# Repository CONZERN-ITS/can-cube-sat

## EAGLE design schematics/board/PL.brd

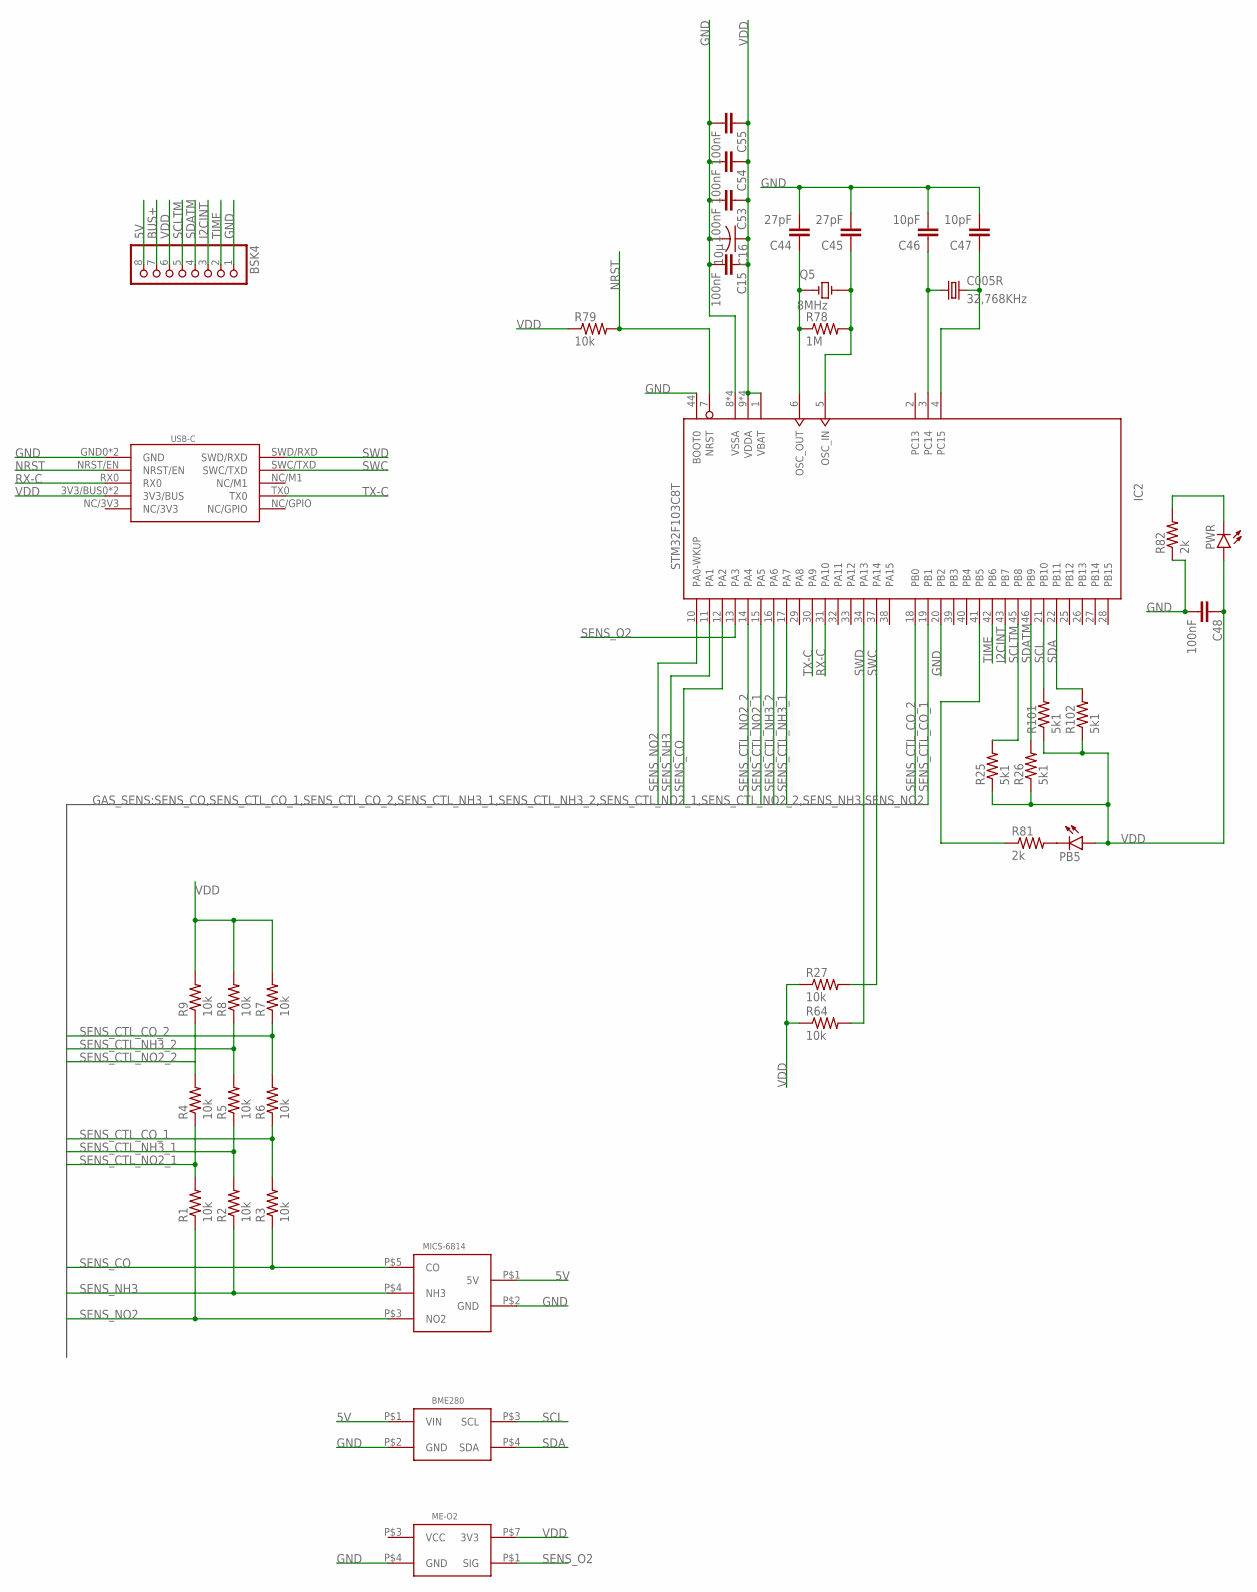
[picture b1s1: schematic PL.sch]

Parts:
BME280: BME280
BSK4: PINHD-1X8; 1X08
C005R: 32,768KHz; C005R
C15, C48, C53, C54, C55: 100nF; C0603
C16: 10µ; C1206
C44, C45: 27pF; C0603
C46, C47: 10pF; C0603
IC2: STM32F103C8T; LQFP48
ME-O2: ME-O2
MICS-6814: MICS-6814
PB5: LEDCHIPLED_0603; CHIPLED_0603
PWR: LEDCHIPLED_0603; CHIPLED_0603
Q5: 8MHz; XTAL_9C-8.000MEEJ-T
R1, R2, R3, R4, R5, R6, R7, R8, R9, R27, R64, R79: 10k; R0603
R25, R26, R101, R102: 5k1; R0603
R78: 1M; R0603
R81, R82: 2k; R0603
USB-C: USB-C

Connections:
5V: BME280.P$1 (VIN), BSK4.8, MICS-6814.P$1 (5V)
BUS+: BSK4.7
GND: BME280.P$2 (GND), BSK4.1, C15.2, C16.2, C44.2, C45.2, C46.2, C47.2, C48.2, C53.2, C54.2, C55.2, IC2.8 (VSSA), IC2.20 (PB2), IC2.23 (VSSA), IC2.35 (VSSA), IC2.44 (BOOT0), IC2.47 (VSSA), ME-O2.P$4 (GND), MICS-6814.P$2 (GND), R82.1, USB-C.GND0 (GND), USB-C.GND1 (GND)
I2CINT: BSK4.3, IC2.43 (PB7)
unnamed: PB5.C, R81.2
unnamed: C44.1, IC2.6 (OSC_OUT), Q5.1, R78.1
unnamed: C45.1, IC2.5 (OSC_IN), Q5.2, R78.2
unnamed: C005R.P$2 (2), C47.1, IC2.4 (PC15)
unnamed: C005R.P$1 (1), C46.1, IC2.3 (PC14)
unnamed: PWR.C, R82.2
unnamed: IC2.41 (PB5), R81.1
NRST: IC2.7 (NRST), R79.2, USB-C.NRST/EN
RX-C: IC2.31 (PA10), USB-C.RX0
SCL: BME280.P$3 (SCL), IC2.21 (PB10), R101.2
SCLTM: BSK4.5, IC2.45 (PB8), R25.2
SDA: BME280.P$4 (SDA), IC2.22 (PB11), R102.2
SDATM: BSK4.4, IC2.46 (PB9), R26.2
SENS_CO: IC2.12 (PA2), MICS-6814.P$5 (CO), R3.1
SENS_CTL_CO_1: IC2.19 (PB1), R3.2, R6.1
SENS_CTL_CO_2: IC2.18 (PB0), R6.2, R7.1
SENS_CTL_NH3_1: IC2.17 (PA7), R2.2, R5.1
SENS_CTL_NH3_2: IC2.16 (PA6), R5.2, R8.1
SENS_CTL_NO2_1: IC2.15 (PA5), R1.2, R4.1
SENS_CTL_NO2_2: IC2.14 (PA4), R4.2, R9.1
SENS_NH3: IC2.11 (PA1), MICS-6814.P$4 (NH3), R2.1
SENS_NO2: IC2.10 (PA0-WKUP), MICS-6814.P$3 (NO2), R1.1
SENS_O2: IC2.13 (PA3), ME-O2.P$1 (SIG)
SWC: IC2.37 (PA14), R27.2, USB-C.SWC/TXD
SWD: IC2.34 (PA13), R64.2, USB-C.SWD/RXD
TIME: BSK4.2, IC2.42 (PB6)
TX-C: IC2.30 (PA9), USB-C.TX0
VDD: BSK4.6, C15.1, C16.1, C48.1, C53.1, C54.1, C55.1, IC2.1 (VBAT), IC2.9 (VDDA), IC2.24 (VDDA), IC2.36 (VDDA), IC2.48 (VDDA), ME-O2.P$7 (3V3), PB5.A, PWR.A, R7.2, R8.2, R9.2, R25.1, R26.1, R27.1, R64.1, R79.1, R101.1, R102.1, USB-C.3V3/BUS0 (3V3/BUS), USB-C.3V3/BUS1 (3V3/BUS)

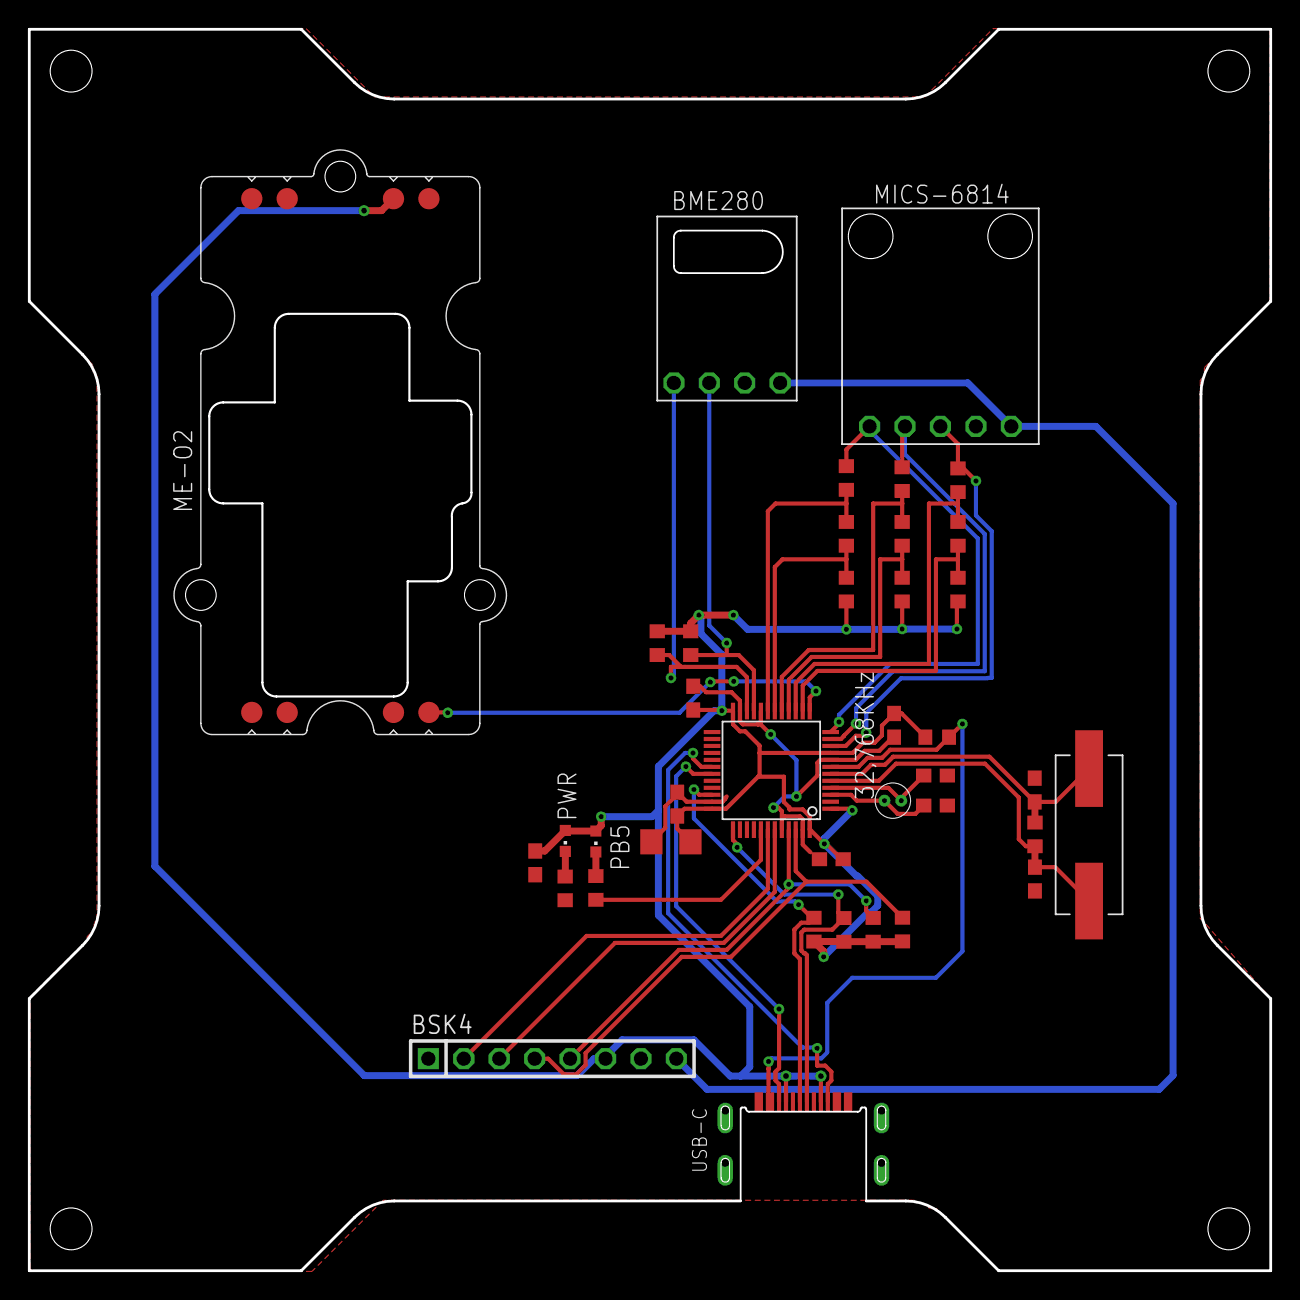
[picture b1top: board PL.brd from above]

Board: 2 copper layers, 89.0 x 89.0 mm, 39 parts (0 on the bottom side), 31 nets.

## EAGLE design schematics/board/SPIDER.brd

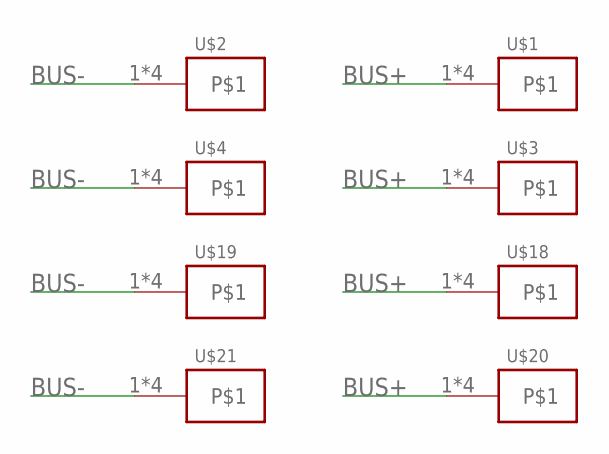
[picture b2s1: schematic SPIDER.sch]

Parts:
U$1, U$2, U$3, U$4, U$18, U$19, U$20, U$21: KCONNECT-

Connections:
BUS+: U$1.1, U$1.2, U$1.3, U$1.4, U$3.1, U$3.2, U$3.3, U$3.4, U$18.1, U$18.2, U$18.3, U$18.4, U$20.1, U$20.2, U$20.3, U$20.4
BUS-: U$2.1, U$2.2, U$2.3, U$2.4, U$4.1, U$4.2, U$4.3, U$4.4, U$19.1, U$19.2, U$19.3, U$19.4, U$21.1, U$21.2, U$21.3, U$21.4

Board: 2 copper layers, 8 parts (0 on the bottom side), 2 nets, no tracks yet.

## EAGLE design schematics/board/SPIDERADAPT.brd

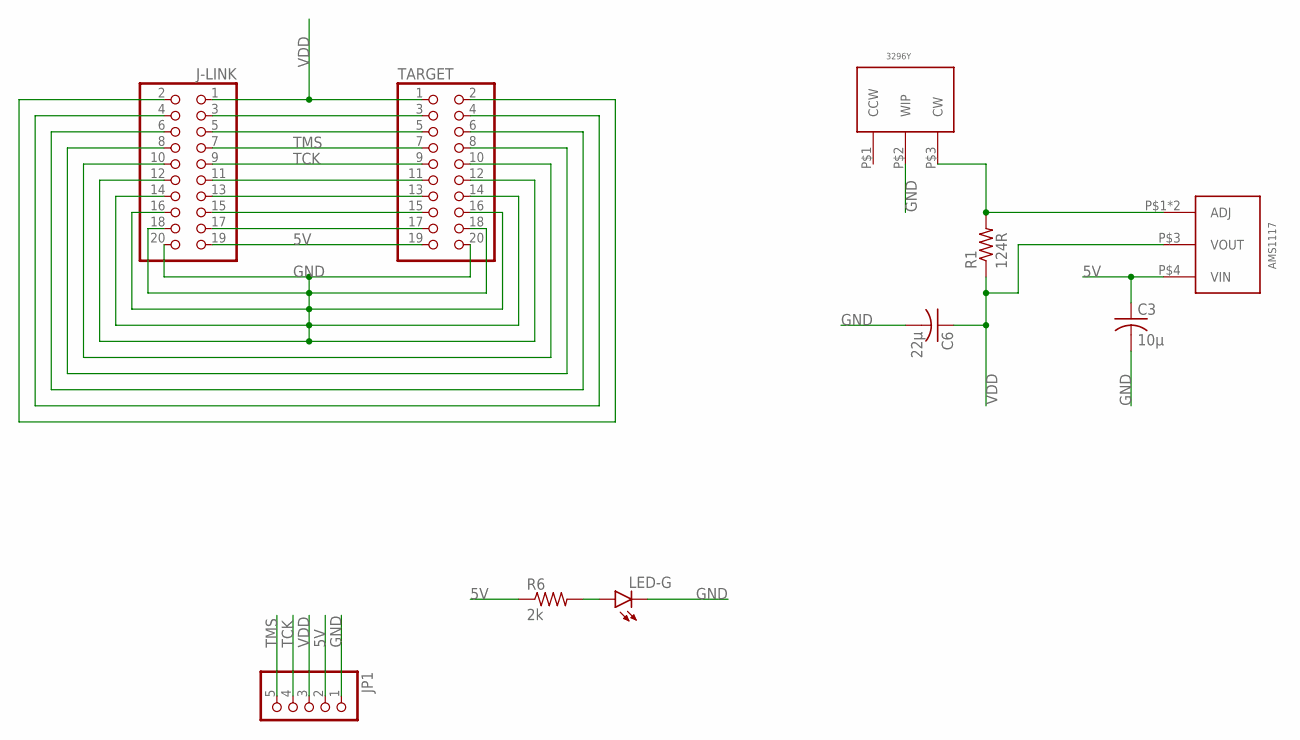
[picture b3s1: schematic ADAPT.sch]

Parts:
3296Y: 3296Y
AMS1117: AMS1117
C3: 10µ; C1206
C6: 22µ; C1206
J-LINK: PINHD-2X10; 2X10
JP1: PINHD-1X5; 1X05
LED-G: LEDCHIPLED_0603; CHIPLED_0603
R1: 124R; R0805
R6: 2k; R0603
TARGET: PINHD-2X10; 2X10

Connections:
5V: AMS1117.P$4 (VIN), C3.1, J-LINK.19, JP1.2, R6.1, TARGET.19
GND1: 3296Y.P$2 (WIP), C3.2, C6.2, J-LINK.12, J-LINK.14, J-LINK.16, J-LINK.18, J-LINK.20, JP1.1, LED-G.C, TARGET.12, TARGET.14, TARGET.16, TARGET.18, TARGET.20
unnamed: J-LINK.3, TARGET.3
unnamed: J-LINK.5, TARGET.5
unnamed: J-LINK.11, TARGET.11
unnamed: J-LINK.13, TARGET.13
unnamed: J-LINK.15, TARGET.15
unnamed: J-LINK.17, TARGET.17
unnamed: J-LINK.10, TARGET.10
unnamed: J-LINK.8, TARGET.8
unnamed: J-LINK.6, TARGET.6
unnamed: J-LINK.4, TARGET.4
unnamed: J-LINK.2, TARGET.2
unnamed 31: 3296Y.P$3 (CW), AMS1117.P$1 (ADJ), AMS1117.P$2 (ADJ), R1.2; also elsewhere on the board
unnamed: LED-G.A, R6.2
TCK: J-LINK.9, JP1.4, TARGET.9
TMS: J-LINK.7, JP1.5, TARGET.7
VDD: AMS1117.P$3 (VOUT), C6.1, J-LINK.1, JP1.3, R1.1, TARGET.1; also elsewhere on the board

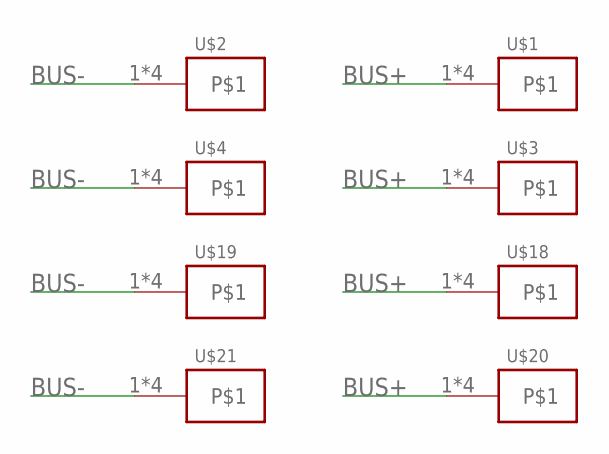
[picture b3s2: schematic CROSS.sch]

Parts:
U$1, U$2, U$3, U$4, U$18, U$19, U$20, U$21: KCONNECT-

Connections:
BUS+: U$1.1, U$1.2, U$1.3, U$1.4, U$3.1, U$3.2, U$3.3, U$3.4, U$18.1, U$18.2, U$18.3, U$18.4, U$20.1, U$20.2, U$20.3, U$20.4
BUS-: U$2.1, U$2.2, U$2.3, U$2.4, U$4.1, U$4.2, U$4.3, U$4.4, U$19.1, U$19.2, U$19.3, U$19.4, U$21.1, U$21.2, U$21.3, U$21.4

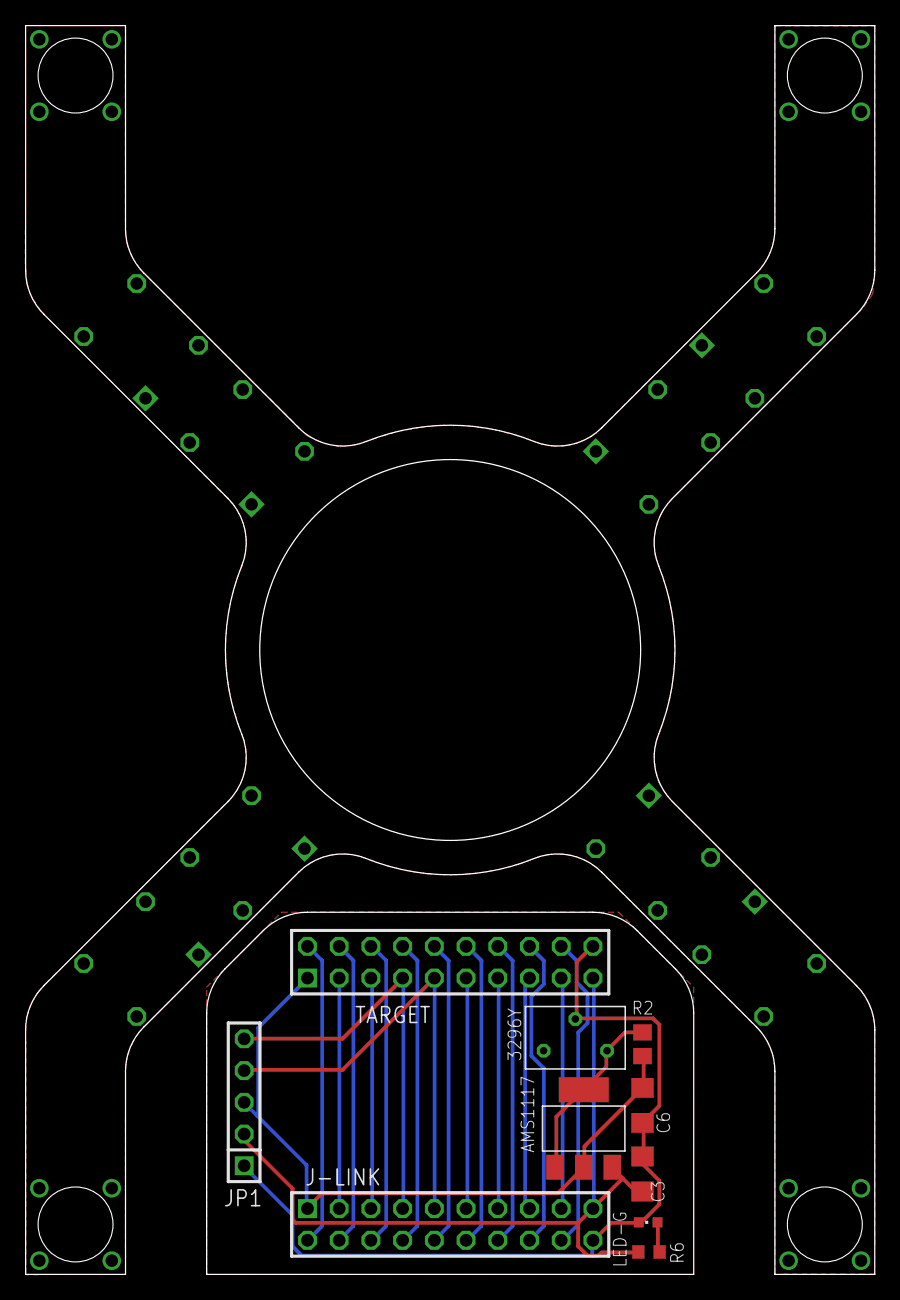
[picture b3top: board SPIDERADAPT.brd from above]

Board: 2 copper layers, 68.0 x 100.0 mm, 18 parts (0 on the bottom side), 20 nets.

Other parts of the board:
R2: 124R; R0805

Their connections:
unnamed 31: R2.2; also elsewhere on the board
VDD: R2.1; also elsewhere on the board

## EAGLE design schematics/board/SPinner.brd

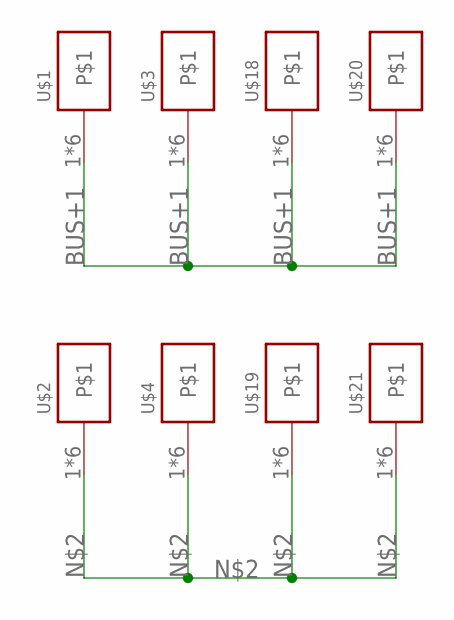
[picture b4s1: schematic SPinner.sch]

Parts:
U$1, U$2, U$3, U$4, U$18, U$19, U$20, U$21: KCONNECT

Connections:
BUS+1: U$1.1, U$1.2, U$1.3, U$1.4, U$1.P$1, U$1.P$2, U$3.1, U$3.2, U$3.3, U$3.4, U$3.P$1, U$3.P$2, U$18.1, U$18.2, U$18.3, U$18.4, U$18.P$1, U$18.P$2, U$20.1, U$20.2, U$20.3, U$20.4, U$20.P$1, U$20.P$2
unnamed: U$2.1, U$2.2, U$2.3, U$2.4, U$2.P$1, U$2.P$2, U$4.1, U$4.2, U$4.3, U$4.4, U$4.P$1, U$4.P$2, U$19.1, U$19.2, U$19.3, U$19.4, U$19.P$1, U$19.P$2, U$21.1, U$21.2, U$21.3, U$21.4, U$21.P$1, U$21.P$2

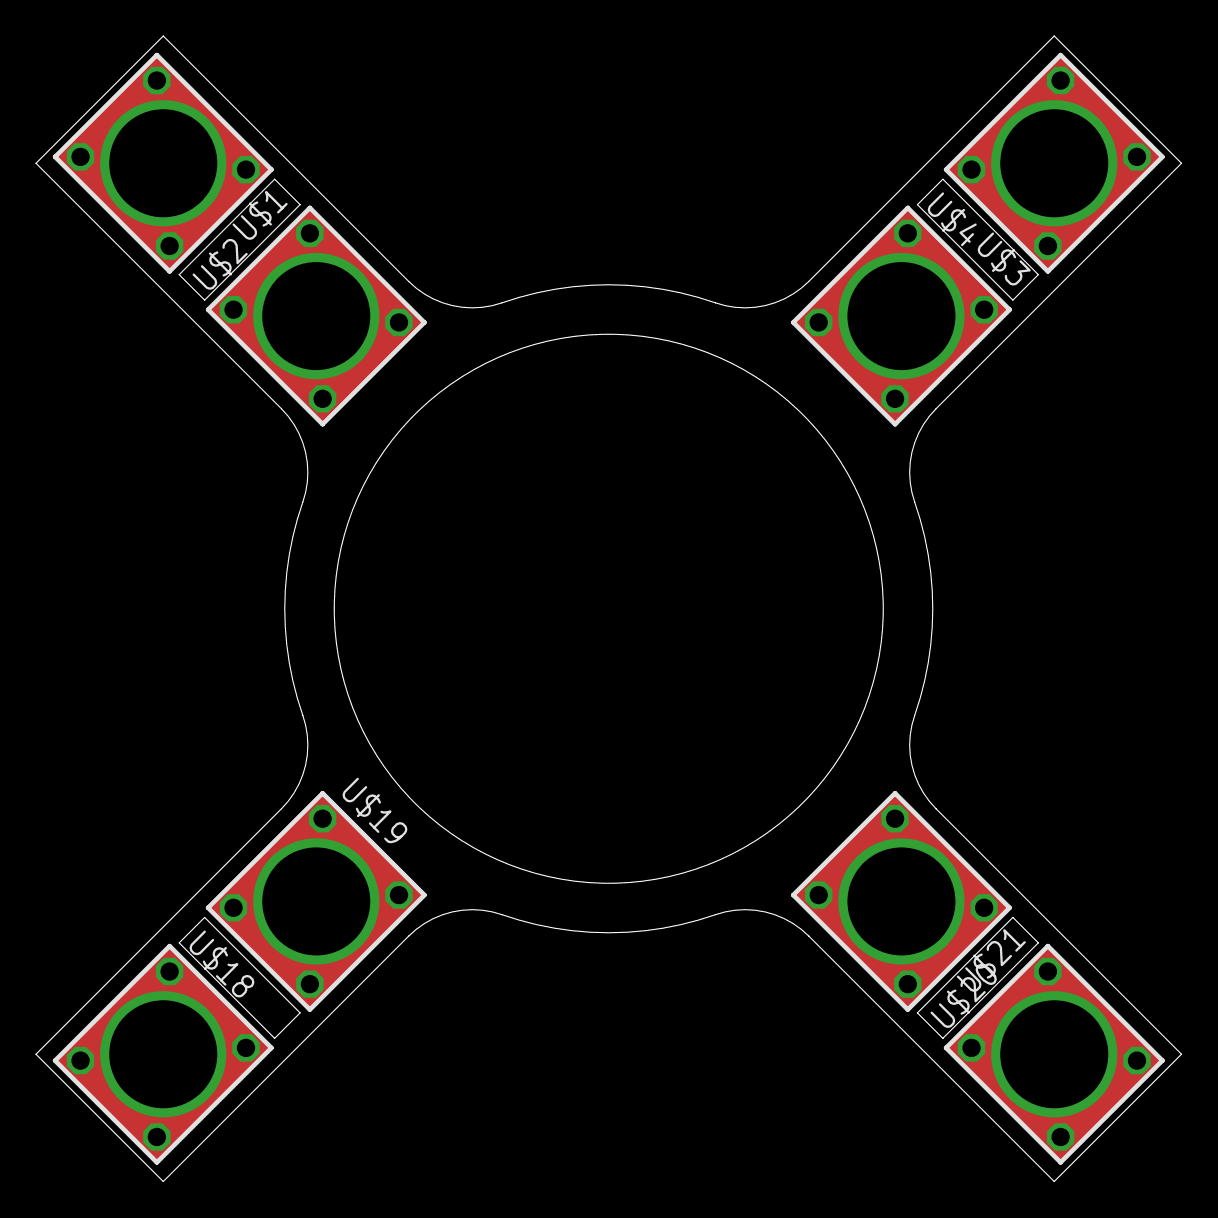
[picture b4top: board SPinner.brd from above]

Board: 2 copper layers, 63.6 x 63.6 mm, 8 parts (0 on the bottom side), 2 nets.

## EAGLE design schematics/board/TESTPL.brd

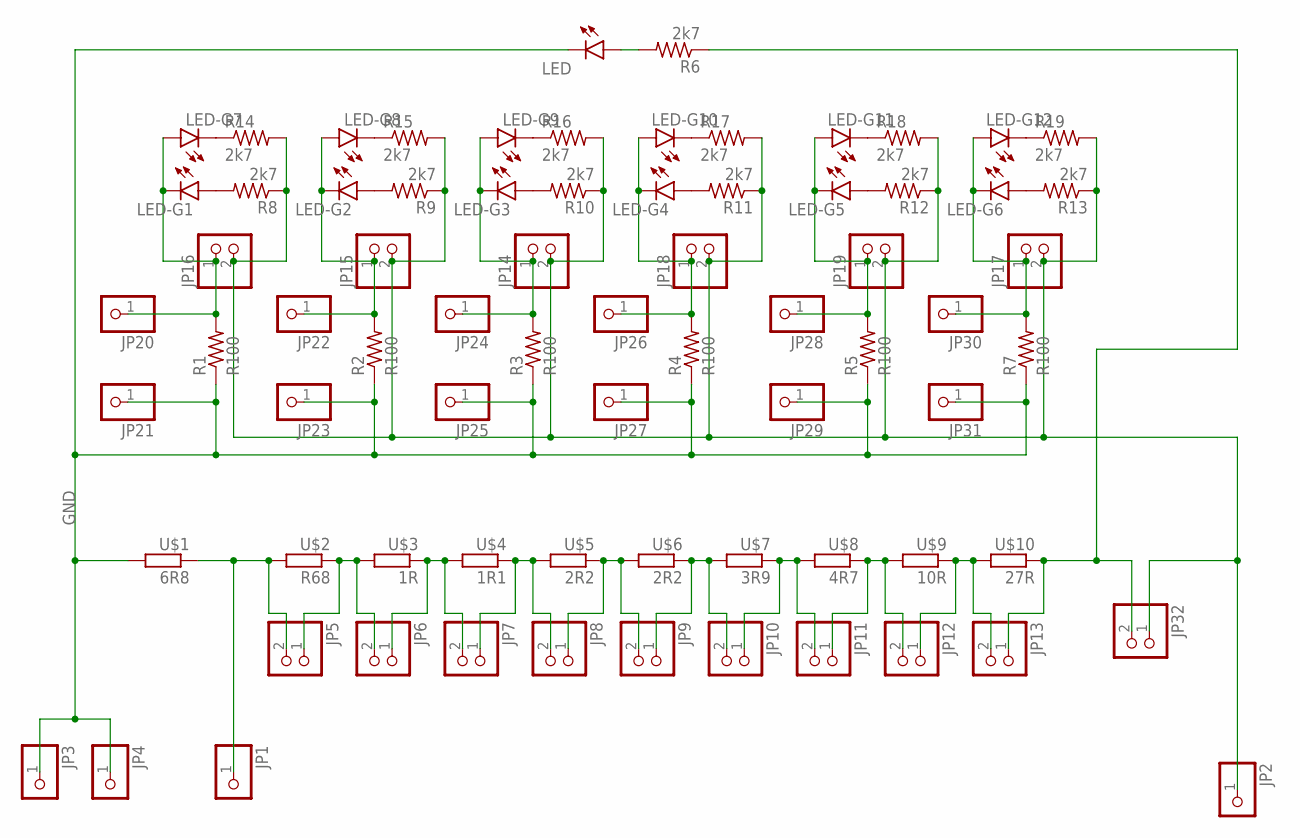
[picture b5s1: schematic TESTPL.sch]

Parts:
JP1, JP2, JP3, JP4, JP20, JP21, JP22, JP23, JP24, JP25, JP26, JP27, JP28, JP29, JP30, JP31: PINHD-1X1; 1X01
JP5, JP6, JP7, JP8, JP9, JP10, JP11, JP12, JP13, JP14, JP15, JP16, JP17, JP18, JP19, JP32: PINHD-1X2; 1X02
LED: LEDCHIPLED_0603; CHIPLED_0603
LED-G1, LED-G2, LED-G3, LED-G4, LED-G5, LED-G6, LED-G7, LED-G8, LED-G9, LED-G10, LED-G11, LED-G12: LEDCHIPLED_0603; CHIPLED_0603
R1, R2, R3, R4, R5, R7: R100; R2512
R6, R8, R9, R10, R11, R12, R13, R14, R15, R16, R17, R18, R19: 2k7; R0603
U$1: 6R8; SQP
U$2: R68; SQP
U$3: 1R; SQP
U$4: 1R1; SQP
U$5, U$6: 2R2; SQP
U$7: 3R9; SQP
U$8: 4R7; SQP
U$9: 10R; SQP
U$10: 27R; SQP

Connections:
GND: JP3.1, JP4.1, JP21.1, JP23.1, JP25.1, JP27.1, JP29.1, JP31.1, LED.C, R1.1, R2.1, R3.1, R4.1, R5.1, R7.1, U$1.P$2 (2)
unnamed: JP1.1, JP5.2, U$1.P$1 (1), U$2.P$2 (2)
unnamed: JP5.1, JP6.2, U$2.P$1 (1), U$3.P$2 (2)
unnamed: JP6.1, JP7.2, U$3.P$1 (1), U$4.P$2 (2)
unnamed: JP7.1, JP8.2, U$4.P$1 (1), U$5.P$2 (2)
unnamed: JP8.1, JP9.2, U$5.P$1 (1), U$6.P$2 (2)
unnamed: JP9.1, JP10.2, U$6.P$1 (1), U$7.P$2 (2)
unnamed: JP10.1, JP11.2, U$7.P$1 (1), U$8.P$2 (2)
unnamed: JP11.1, JP12.2, U$8.P$1 (1), U$9.P$2 (2)
unnamed: JP12.1, JP13.2, U$9.P$1 (1), U$10.P$2 (2)
unnamed: JP17.1, JP30.1, LED-G6.C, LED-G12.A, R7.2
unnamed: JP2.1, JP14.2, JP15.2, JP16.2, JP17.2, JP18.2, JP19.2, JP32.1, R8.1, R9.1, R10.1, R11.1, R12.1, R13.1, R14.2, R15.2, R16.2, R17.2, R18.2, R19.2
unnamed: JP19.1, JP28.1, LED-G5.C, LED-G11.A, R5.2
unnamed: JP18.1, JP26.1, LED-G4.C, LED-G10.A, R4.2
unnamed: JP14.1, JP24.1, LED-G3.C, LED-G9.A, R3.2
unnamed: JP15.1, JP22.1, LED-G2.C, LED-G8.A, R2.2
unnamed: JP16.1, JP20.1, LED-G1.C, LED-G7.A, R1.2
unnamed: JP13.1, JP32.2, R6.1, U$10.P$1 (1)
unnamed: LED-G1.A, R8.2
unnamed: LED-G2.A, R9.2
unnamed: LED-G3.A, R10.2
unnamed: LED-G4.A, R11.2
unnamed: LED-G5.A, R12.2
unnamed: LED-G6.A, R13.2
unnamed: LED-G8.C, R15.1
unnamed: LED-G7.C, R14.1
unnamed: LED-G9.C, R16.1
unnamed: LED-G10.C, R17.1
unnamed: LED-G11.C, R18.1
unnamed: LED-G12.C, R19.1
unnamed: LED.A, R6.2

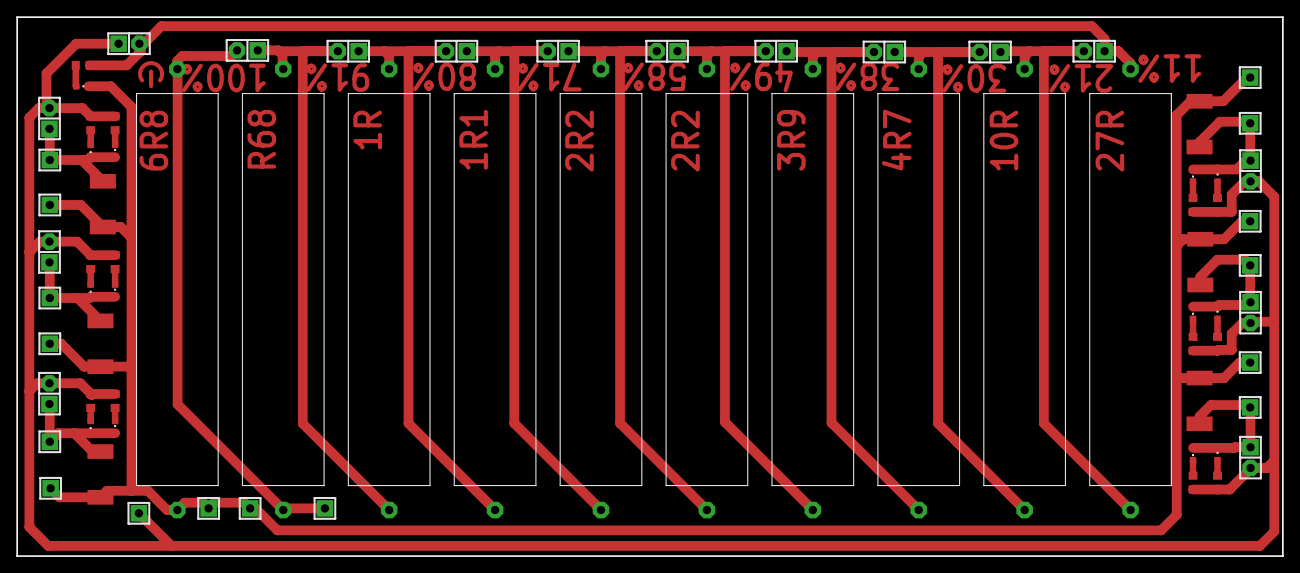
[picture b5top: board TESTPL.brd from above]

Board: 2 copper layers, 155.0 x 66.0 mm, 74 parts (0 on the bottom side), 31 nets.

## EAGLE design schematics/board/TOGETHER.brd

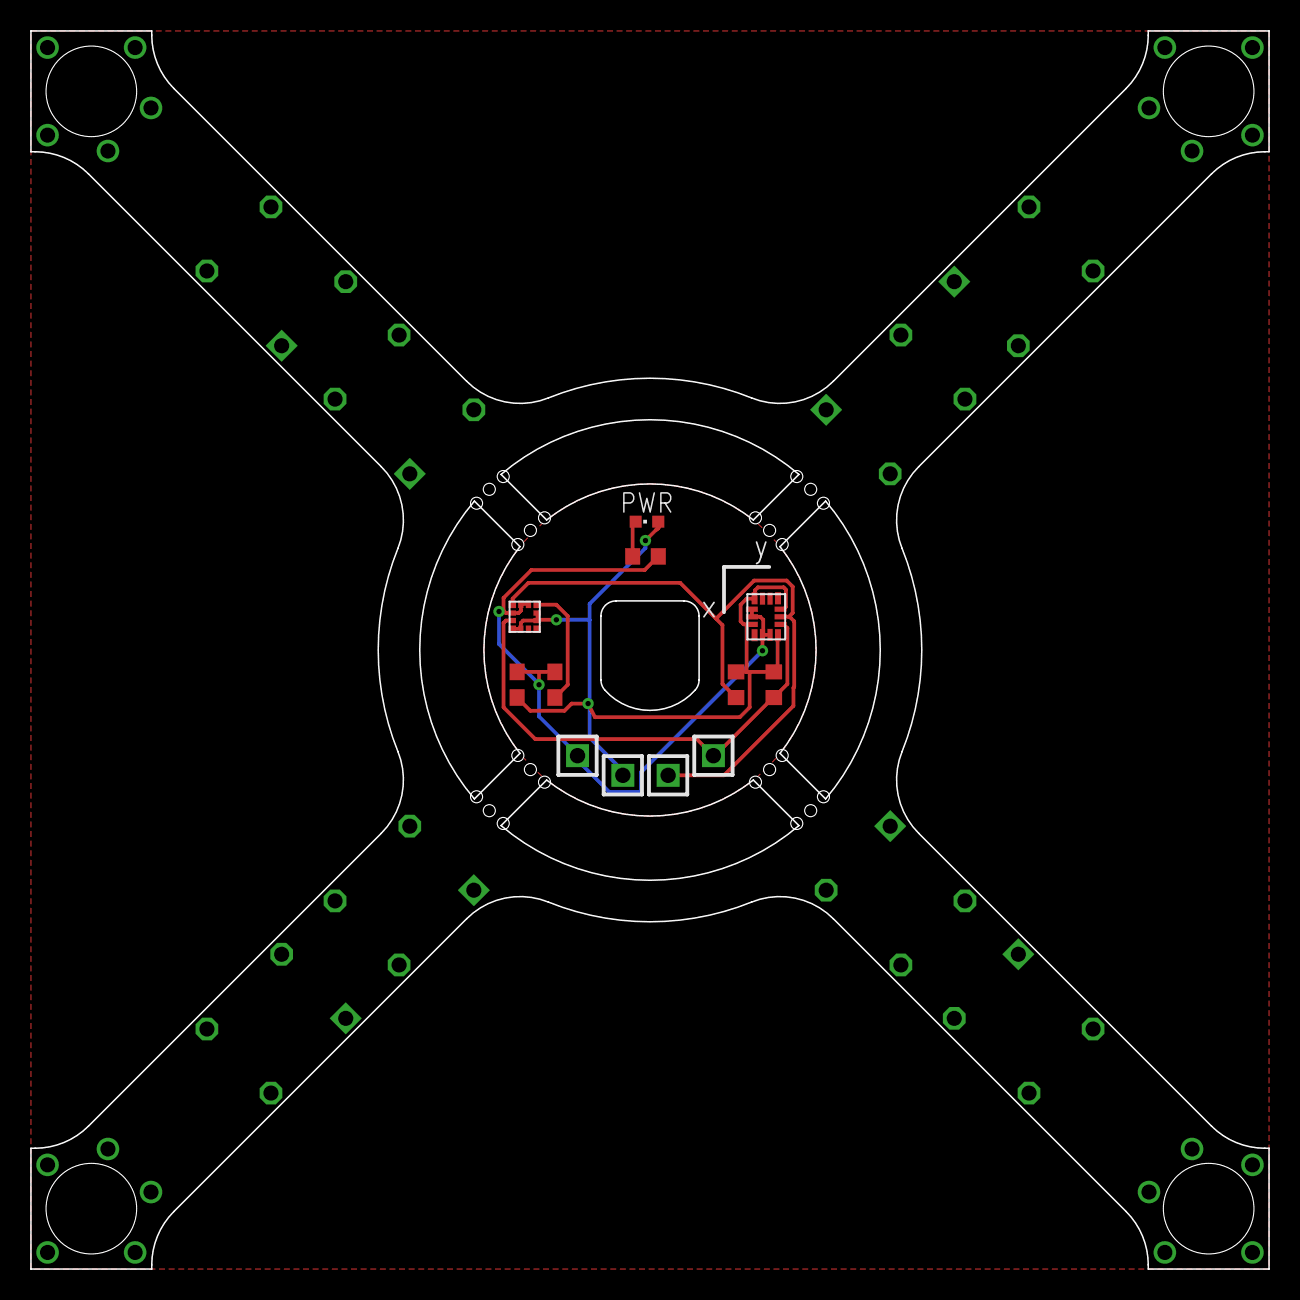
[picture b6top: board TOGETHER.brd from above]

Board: 2 copper layers, 82.0 x 82.0 mm, 20 parts (0 on the bottom side), 8 nets.

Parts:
3V3: 1X01
C1, C10: 0,1µ; C0603
GND: 1X01
LIS3MDL: LIS3MDL
LSM6DS3: LSM6DS3
PWR: CHIPLED_0603
R1: 2k; R0603
R101, R102: 5k1; R0603
SCL: 1X01
SDA: 1X01
U$1, U$2, U$3, U$4, U$18, U$19, U$20, U$21: KCONNECT-

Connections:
BUS+: U$1.1, U$1.2, U$1.3, U$1.4, U$3.1, U$3.2, U$3.3, U$3.4, U$18.1, U$18.2, U$18.3, U$18.4, U$20.1, U$20.2, U$20.3, U$20.4
BUS-: U$2.1, U$2.2, U$2.3, U$2.4, U$4.1, U$4.2, U$4.3, U$4.4, U$19.1, U$19.2, U$19.3, U$19.4, U$21.1, U$21.2, U$21.3, U$21.4
GND: C1.2, C10.2, GND.1, LIS3MDL.P$8, LIS3MDL.P$9, LIS3MDL.P$11, LSM6DS3.P$5, LSM6DS3.P$6, LSM6DS3.P$9, LSM6DS3.P$10, R1.1
unnamed: PWR.C, R1.2
unnamed: C10.1, LIS3MDL.P$7
SCL: LIS3MDL.P$10, LSM6DS3.P$13, R101.2, SCL.1
SDA: LIS3MDL.P$12, LSM6DS3.P$12, R102.2, SDA.1
VDD1: 3V3.1, C1.1, LIS3MDL.P$1, LIS3MDL.P$2, LIS3MDL.P$5, LIS3MDL.P$6, LSM6DS3.P$4, LSM6DS3.P$7, LSM6DS3.P$11, LSM6DS3.P$14, PWR.A, R101.1, R102.1

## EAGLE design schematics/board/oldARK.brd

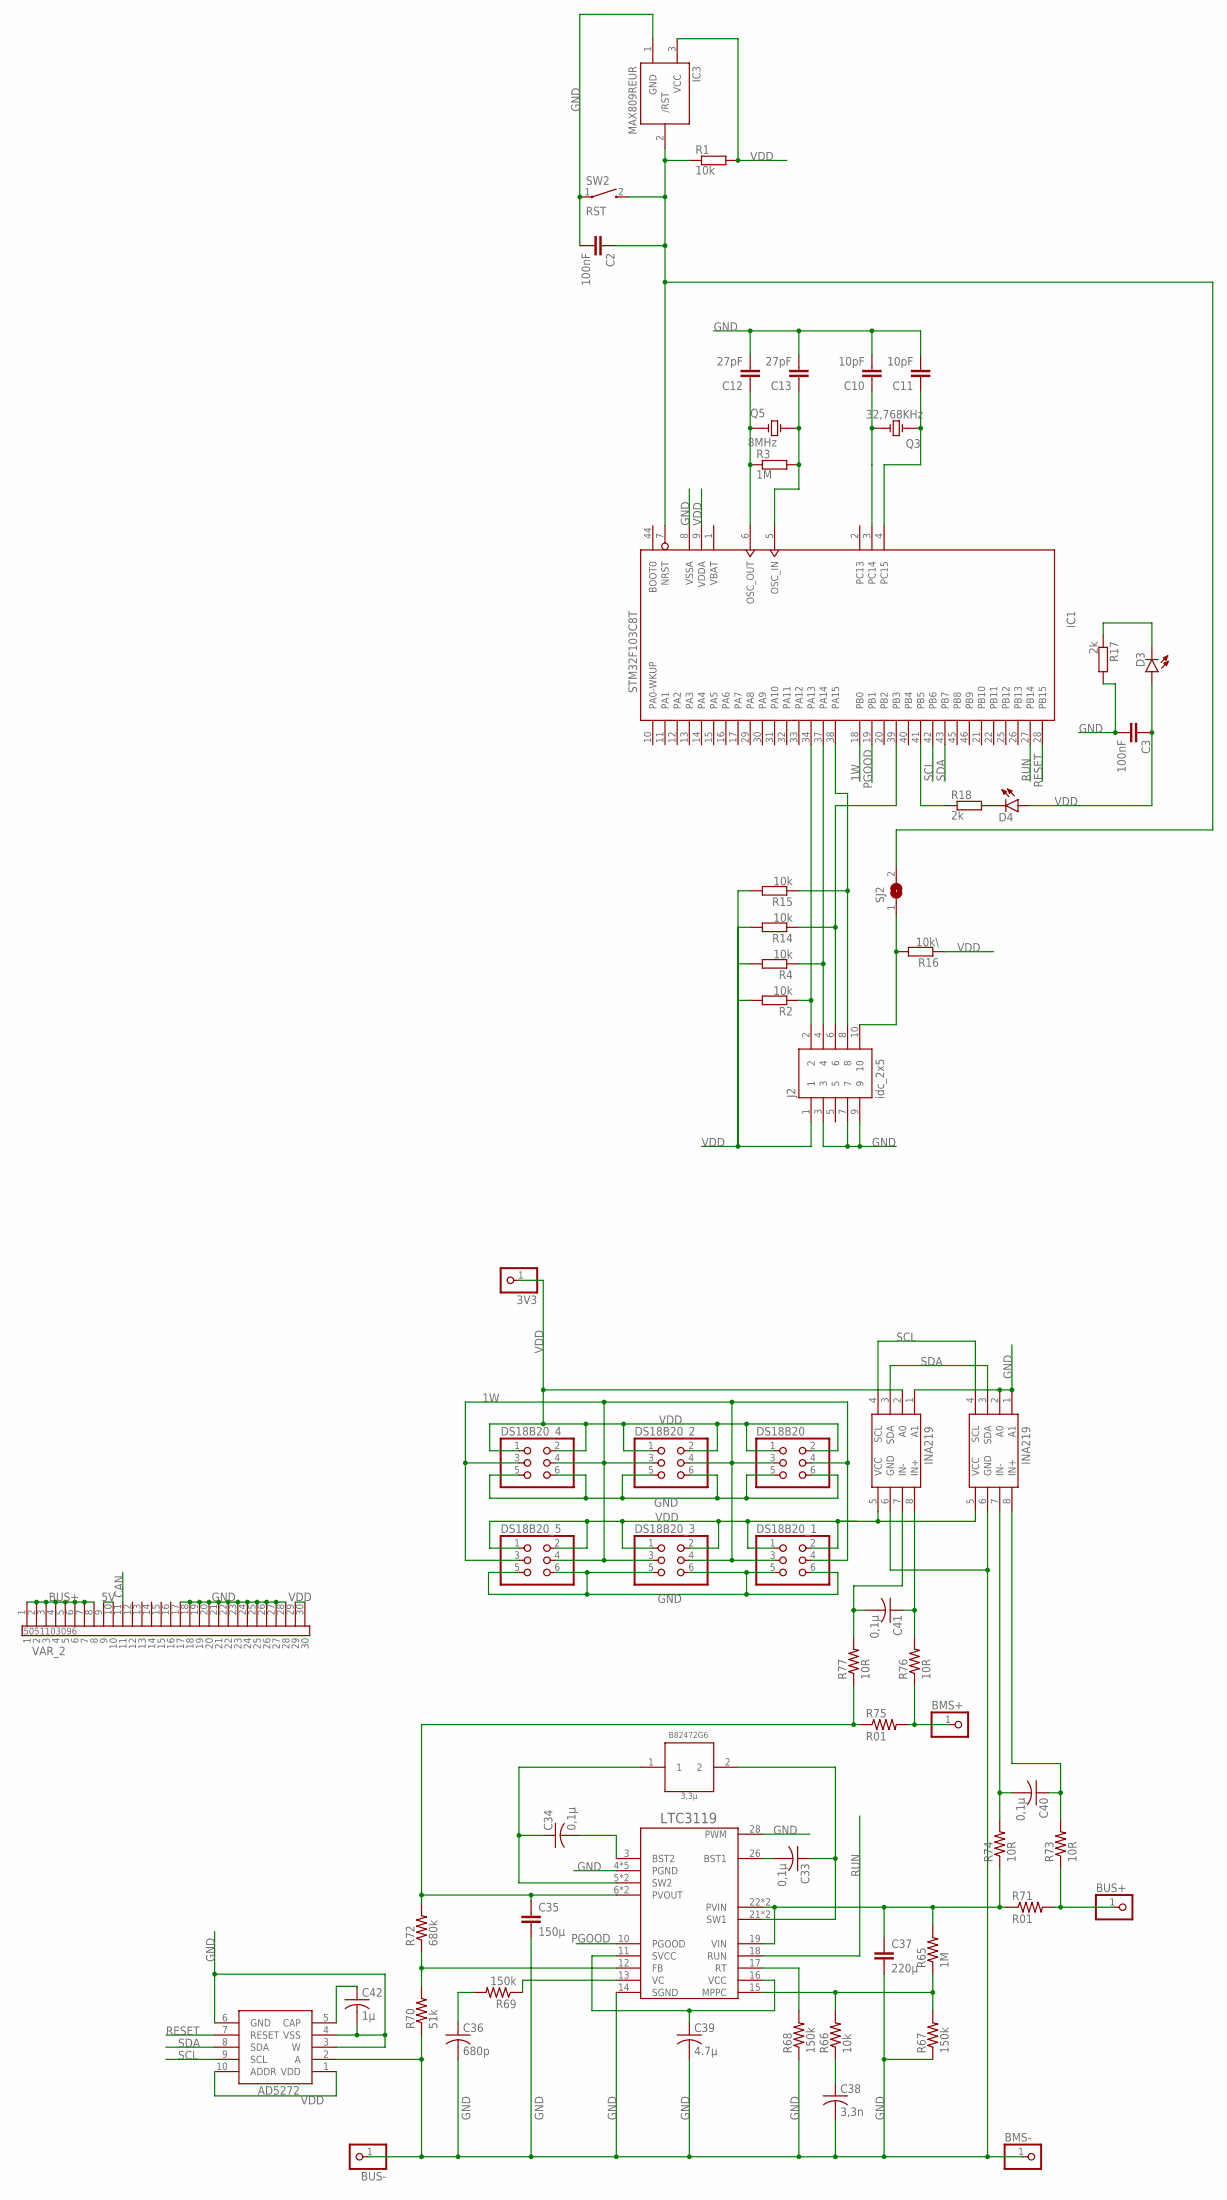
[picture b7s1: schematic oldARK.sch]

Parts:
3,3µH: 3,3µ; B82472G6
3V3: PINHD-1X1; 1X01
BMS+: PINHD-1X1; 1X01
BMS-: PINHD-1X1; 1X01
BUS+: PINHD-1X1; 1X01
BUS-: PINHD-1X1; 1X01
C2, C3: 100nF; C0603
C10, C11: 10pF; C0603
C12, C13: 27pF; C0603
C33, C34, C40, C41: 0,1µ; C0603
C35: 150µ; ECAP150
C36: 680p; C1206
C37: 220µ; ECAP220
C38: 3,3n; C1206
C39: 4.7µ; C1206
C42: 1µ; C0603
D3, D4: HLMP6
DS18B20, DS18B20_1, DS18B20_2, DS18B20_3, DS18B20_4, DS18B20_5: PINHD-2X3M; 2X03M
IC1: STM32F103C8T; LQFP48
IC3: MAX809REUR; SOT23
J2: idc_2x5; CNC_3221-10-0100-00
Q3: 32,768KHz; XTAL_9C-8.000MEEJ-T
Q5: 8MHz; XTAL_9C-8.000MEEJ-T
R1, R2, R4, R14, R15: 10k; BVS
R3: 1M; BVS
R16: 10k\; BVS
R17, R18: 2k; BVS
R65: 1M; R0603
R66: 10k; R0603
R67, R68, R69: 150k; R0603
R70: 51k; R0603
R71, R75: R01; R2512
R72: 680k; R0603
R73, R74, R76, R77: 10R; R0603
SJ2: SJW
SW2: RST; SW_1437566-3
U$4: 5051103096
U$57, U$58: INA219AID
U$59: LTC3119
U$60: AD5272

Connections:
1W: DS18B20.3, DS18B20.4, DS18B20_1.3, DS18B20_1.4, DS18B20_2.3, DS18B20_2.4, DS18B20_3.3, DS18B20_3.4, DS18B20_4.3, DS18B20_4.4, DS18B20_5.3, DS18B20_5.4, IC1.18 (PB0)
5V: U$4.9, U$4.10
BUS+: U$4.1, U$4.2, U$4.3, U$4.4, U$4.5, U$4.6, U$4.7, U$4.8
GND: BMS-.1, BUS-.1, C2.2, C3.2, C10.2, C11.2, C12.2, C13.2, C35.P$2 (2), C36.2, C37.P$2 (2), C38.2, C39.2, C42.2, DS18B20.5, DS18B20.6, DS18B20_1.5, DS18B20_1.6, DS18B20_2.5, DS18B20_2.6, DS18B20_3.5, DS18B20_3.6, DS18B20_4.5, DS18B20_4.6, DS18B20_5.5, DS18B20_5.6, IC1.8 (VSSA), IC3.1 (GND), J2.3, J2.7, J2.9, R17.1, R67.1, R68.1, R70.1, SW2.1, U$4.17, U$4.18, U$4.19, U$4.20, U$4.21, U$4.22, U$4.23, U$4.24, U$4.25, U$4.26, U$4.27, U$4.28, U$57.1 (A1), U$57.6 (GND), U$58.1 (A1), U$58.2 (A0), U$58.6 (GND), U$59.4 (PGND), U$59.9 (PGND), U$59.14 (SGND), U$59.20 (PGND), U$59.25 (PGND), U$59.28 (PWM), U$59.29 (PGND), U$60.2 (A), U$60.3 (W), U$60.4 (VSS), U$60.6 (GND)
unnamed: C2.1, IC1.7 (NRST), IC3.2 (/RST), R1.2, SJ2.2, SW2.2
unnamed: C11.1, IC1.4 (PC15), Q3.1
unnamed: C10.1, IC1.3 (PC14), Q3.2
unnamed: IC1.34 (PA13), J2.2, R2.2
unnamed: C12.1, IC1.6 (OSC_OUT), Q5.1, R3.2
unnamed: C13.1, IC1.5 (OSC_IN), Q5.2, R3.1
unnamed: IC1.37 (PA14), J2.4, R4.2
unnamed: IC1.38 (PA15), J2.8, R15.2
unnamed: IC1.39 (PB3), J2.6, R14.2
unnamed: J2.10, R16.1, SJ2.1
unnamed: D3.K, R17.2
unnamed: D4.K, R18.1
unnamed: IC1.41 (PB5), R18.2
unnamed: C34.2, U$59.3 (BST2)
unnamed: 3,3µH.2, C33.1, U$59.21 (SW1), U$59.24 (SW1)
unnamed: 3,3µH.1, C34.1, U$59.5 (SW2), U$59.8 (SW2)
unnamed: C35.P$1 (1), R72.2, R75.1, R77.1, U$59.6 (PVOUT), U$59.7 (PVOUT)
unnamed: R69.1, U$59.13 (VC)
unnamed: C36.1, R69.2
unnamed: C37.P$1 (1), R65.2, R71.1, R74.1, U$59.19 (VIN), U$59.22 (PVIN), U$59.23 (PVIN)
unnamed: R65.1, R66.2, R67.2, U$59.15 (MPPC)
unnamed: C38.1, R66.1
unnamed: C39.1, U$59.11 (SVCC), U$59.16 (VCC)
unnamed: C40.2, R74.2, U$58.7 (IN-)
unnamed: R68.2, U$59.17 (RT)
unnamed: R70.2, R72.1, U$59.12 (FB)
unnamed: C33.2, U$59.26 (BST1)
unnamed: BUS+.1, R71.2, R73.1
unnamed: C40.1, R73.2, U$58.8 (IN+)
unnamed: BMS+.1, R75.2, R76.1
unnamed: C41.1, R76.2, U$57.8 (IN+)
unnamed: C41.2, R77.2, U$57.7 (IN-)
unnamed: C42.1, U$60.5 (CAP)
PGOOD: IC1.19 (PB1), U$59.10 (PGOOD)
RESET: IC1.28 (PB15), U$60.7 (RESET)
RUN: IC1.27 (PB14), U$59.18 (RUN)
SCL: IC1.42 (PB6), U$57.4 (SCL), U$58.4 (SCL), U$60.9 (SCL)
SDA: IC1.43 (PB7), U$57.3 (SDA), U$58.3 (SDA), U$60.8 (SDA)
VBAT: IC1.1 (VBAT)
VDD: 3V3.1, C3.1, D3.A, D4.A, DS18B20.1, DS18B20.2, DS18B20_1.1, DS18B20_1.2, DS18B20_2.1, DS18B20_2.2, DS18B20_3.1, DS18B20_3.2, DS18B20_4.1, DS18B20_4.2, DS18B20_5.1, DS18B20_5.2, IC1.9 (VDDA), IC1.24 (VDD), IC1.36 (VDD), IC1.48 (VDD), IC3.3 (VCC), J2.1, R1.1, R2.1, R4.1, R14.1, R15.1, R16.2, U$4.29, U$4.30, U$57.2 (A0), U$57.5 (VCC), U$58.5 (VCC), U$60.1 (VDD), U$60.10 (ADDR)
VSS: IC1.23 (VSS), IC1.35 (VSS), IC1.47 (VSS)

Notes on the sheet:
VAR_2

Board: 2 copper layers, 64 parts (0 on the bottom side), 44 nets, no tracks yet.
